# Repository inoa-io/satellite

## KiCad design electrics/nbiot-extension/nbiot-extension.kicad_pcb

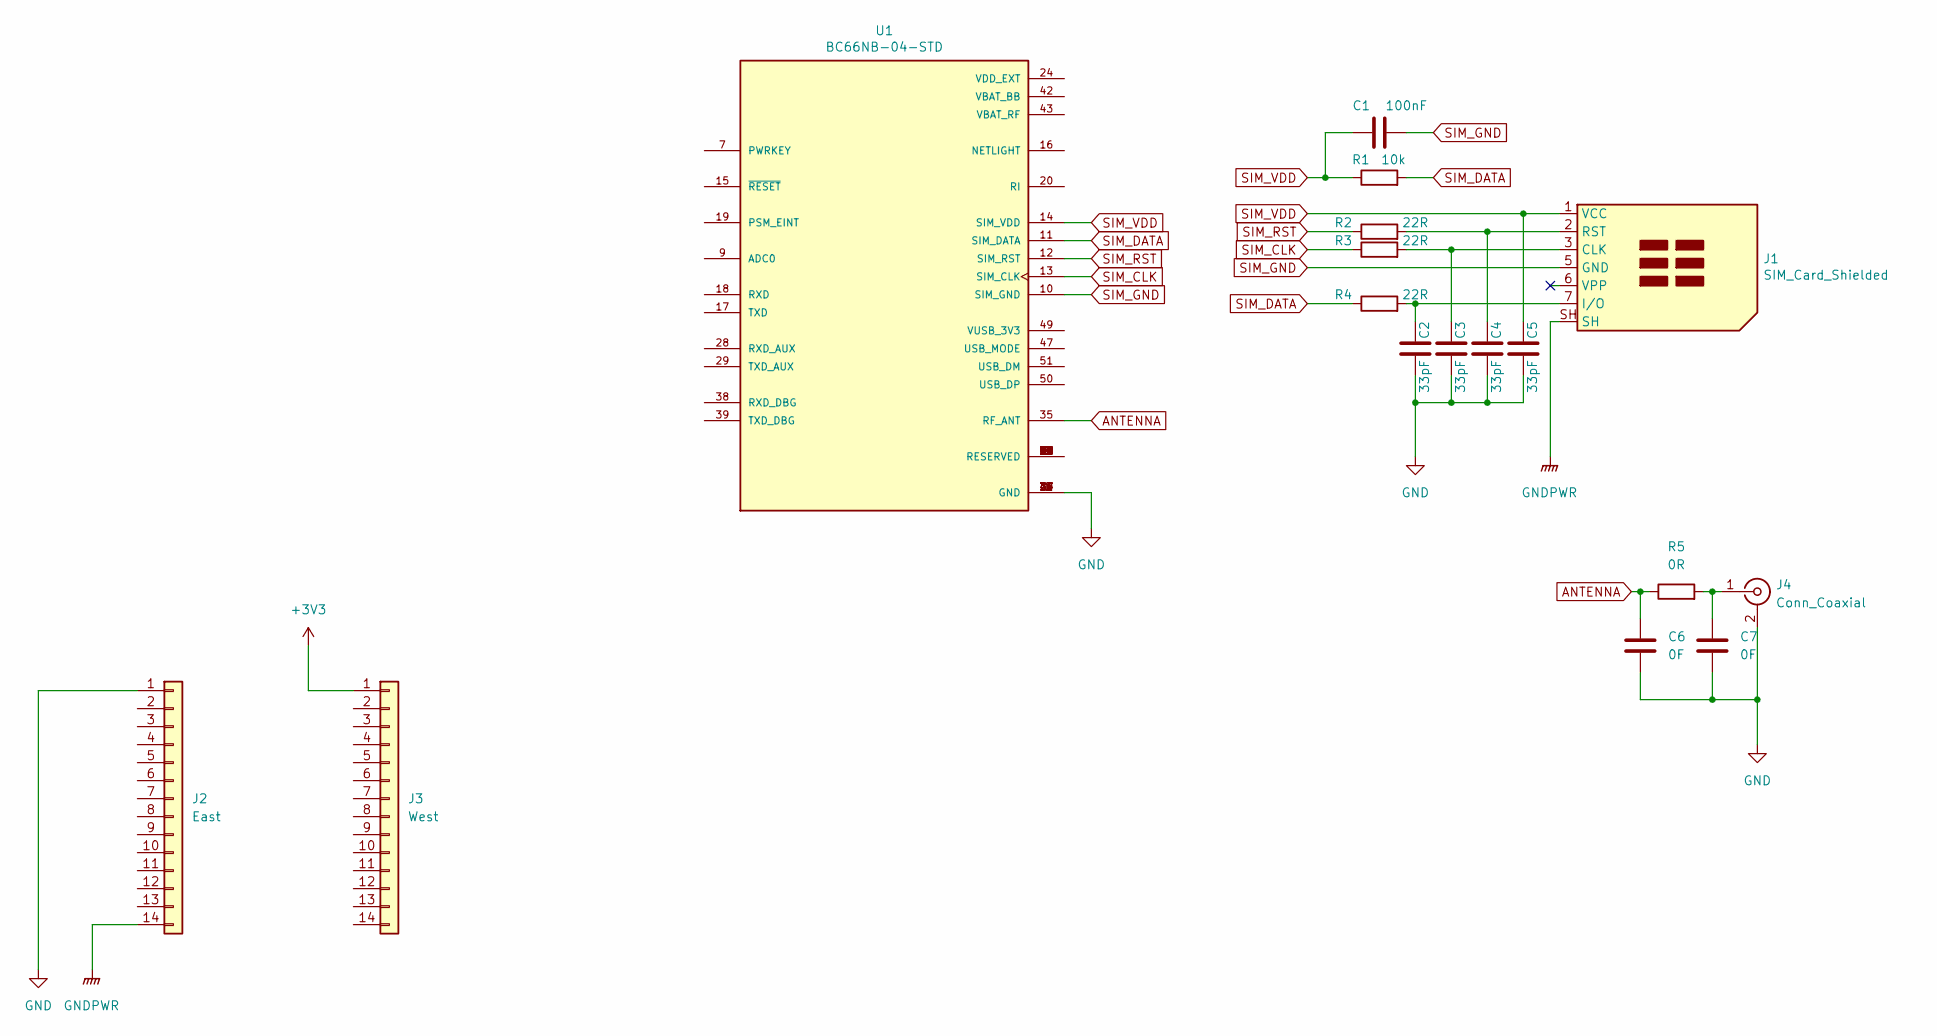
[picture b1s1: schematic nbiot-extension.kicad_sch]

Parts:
C1: 100nF; C_1206_3216Metric_Pad1.33x1.80mm_HandSolder
C2, C3, C4, C5: 33pF; C_1206_3216Metric_Pad1.33x1.80mm_HandSolder
C6, C7: 0F; C_0603_1608Metric_Pad1.08x0.95mm_HandSolder
J1: SIM_Card_Shielded; microSIM_JAE_SF53S006VCBR2000
J2: East; PinHeader_1x14_P2.54mm_Vertical
J3: West; PinHeader_1x14_P2.54mm_Vertical
J4: Conn_Coaxial; U.FL_Hirose_U.FL-R-SMT-1_Vertical
R1: 10k; R_1206_3216Metric_Pad1.30x1.75mm_HandSolder
R2, R3, R4: 22R; R_1206_3216Metric_Pad1.30x1.75mm_HandSolder
R5: 0R; R_0603_1608Metric_Pad0.98x0.95mm_HandSolder
U1: BC66NB-04-STD; XCVR_BC66NB-04-STD

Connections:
+3V3: J3.1
ANTENNA: C6.1, R5.1, U1.35 (RF_ANT); also elsewhere on the board
GND: C2.2, C3.2, C4.2, C5.2, C6.2, C7.2, J2.1, J4.2 (Ext), U1.1 (GND), U1.27 (GND), U1.34 (GND), U1.36 (GND), U1.37 (GND), U1.40 (GND), U1.41 (GND)
GNDPWR: J1.SH, J2.14
unnamed: C2.1, J1.7 (I/O), R4.2
unnamed: C3.1, J1.3 (CLK), R3.2
unnamed: C4.1, J1.2 (RST), R2.2
unnamed 7: C7.1, J4.1 (In), R5.2; also elsewhere on the board
unnamed: U1.2 (RESERVED), U1.3 (RESERVED), U1.4 (RESERVED), U1.5 (RESERVED), U1.6 (RESERVED), U1.8 (RESERVED), U1.21 (RESERVED), U1.22 (RESERVED), U1.23 (RESERVED), U1.25 (RESERVED), U1.26 (RESERVED), U1.30 (RESERVED), U1.31 (RESERVED), U1.32 (RESERVED), U1.33 (RESERVED), U1.44 (RESERVED), U1.45 (RESERVED), U1.46 (RESERVED), U1.48 (RESERVED), U1.52 (RESERVED), U1.53 (RESERVED), U1.54 (RESERVED), U1.55 (RESERVED), U1.56 (RESERVED), U1.57 (RESERVED), U1.58 (RESERVED)
SIM_CLK: R3.1, U1.13 (SIM_CLK)
SIM_DATA: R1.2, R4.1, U1.11 (SIM_DATA)
SIM_GND: C1.2, J1.5 (GND), U1.10 (SIM_GND)
SIM_RST: R2.1, U1.12 (SIM_RST)
SIM_VDD: C1.1, C5.1, J1.1 (VCC), R1.1, U1.14 (SIM_VDD)

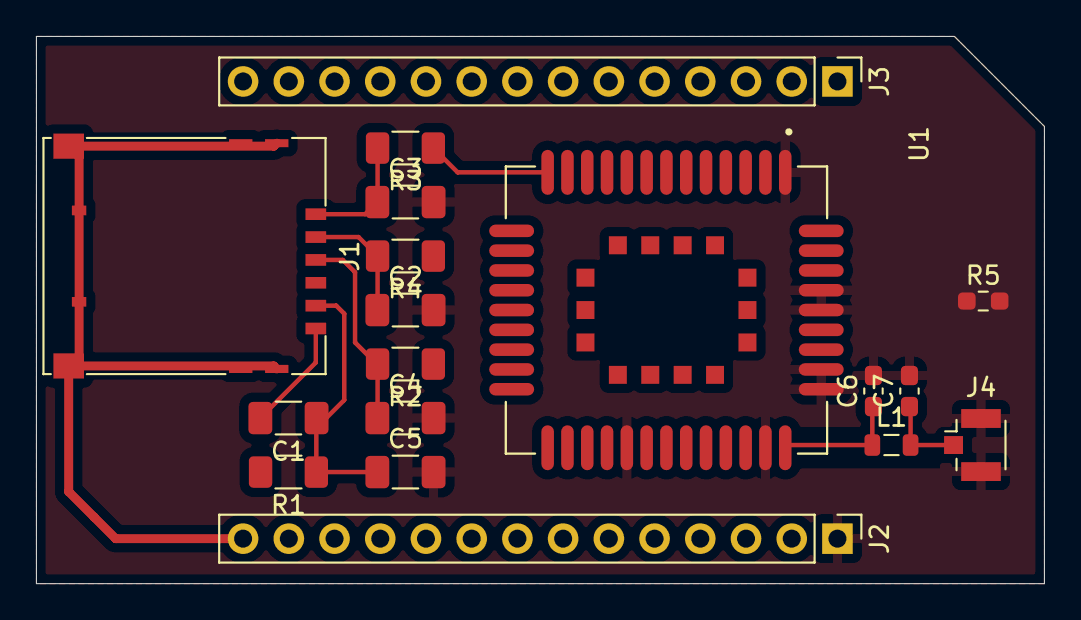
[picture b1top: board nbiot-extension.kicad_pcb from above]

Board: 2 copper layers, 56.0 x 30.4 mm, 18 parts (0 on the bottom side), 13 nets.

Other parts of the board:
L1: L; L_0805_2012Metric

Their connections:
ANTENNA: L1.1; also elsewhere on the board
unnamed 7: L1.2; also elsewhere on the board

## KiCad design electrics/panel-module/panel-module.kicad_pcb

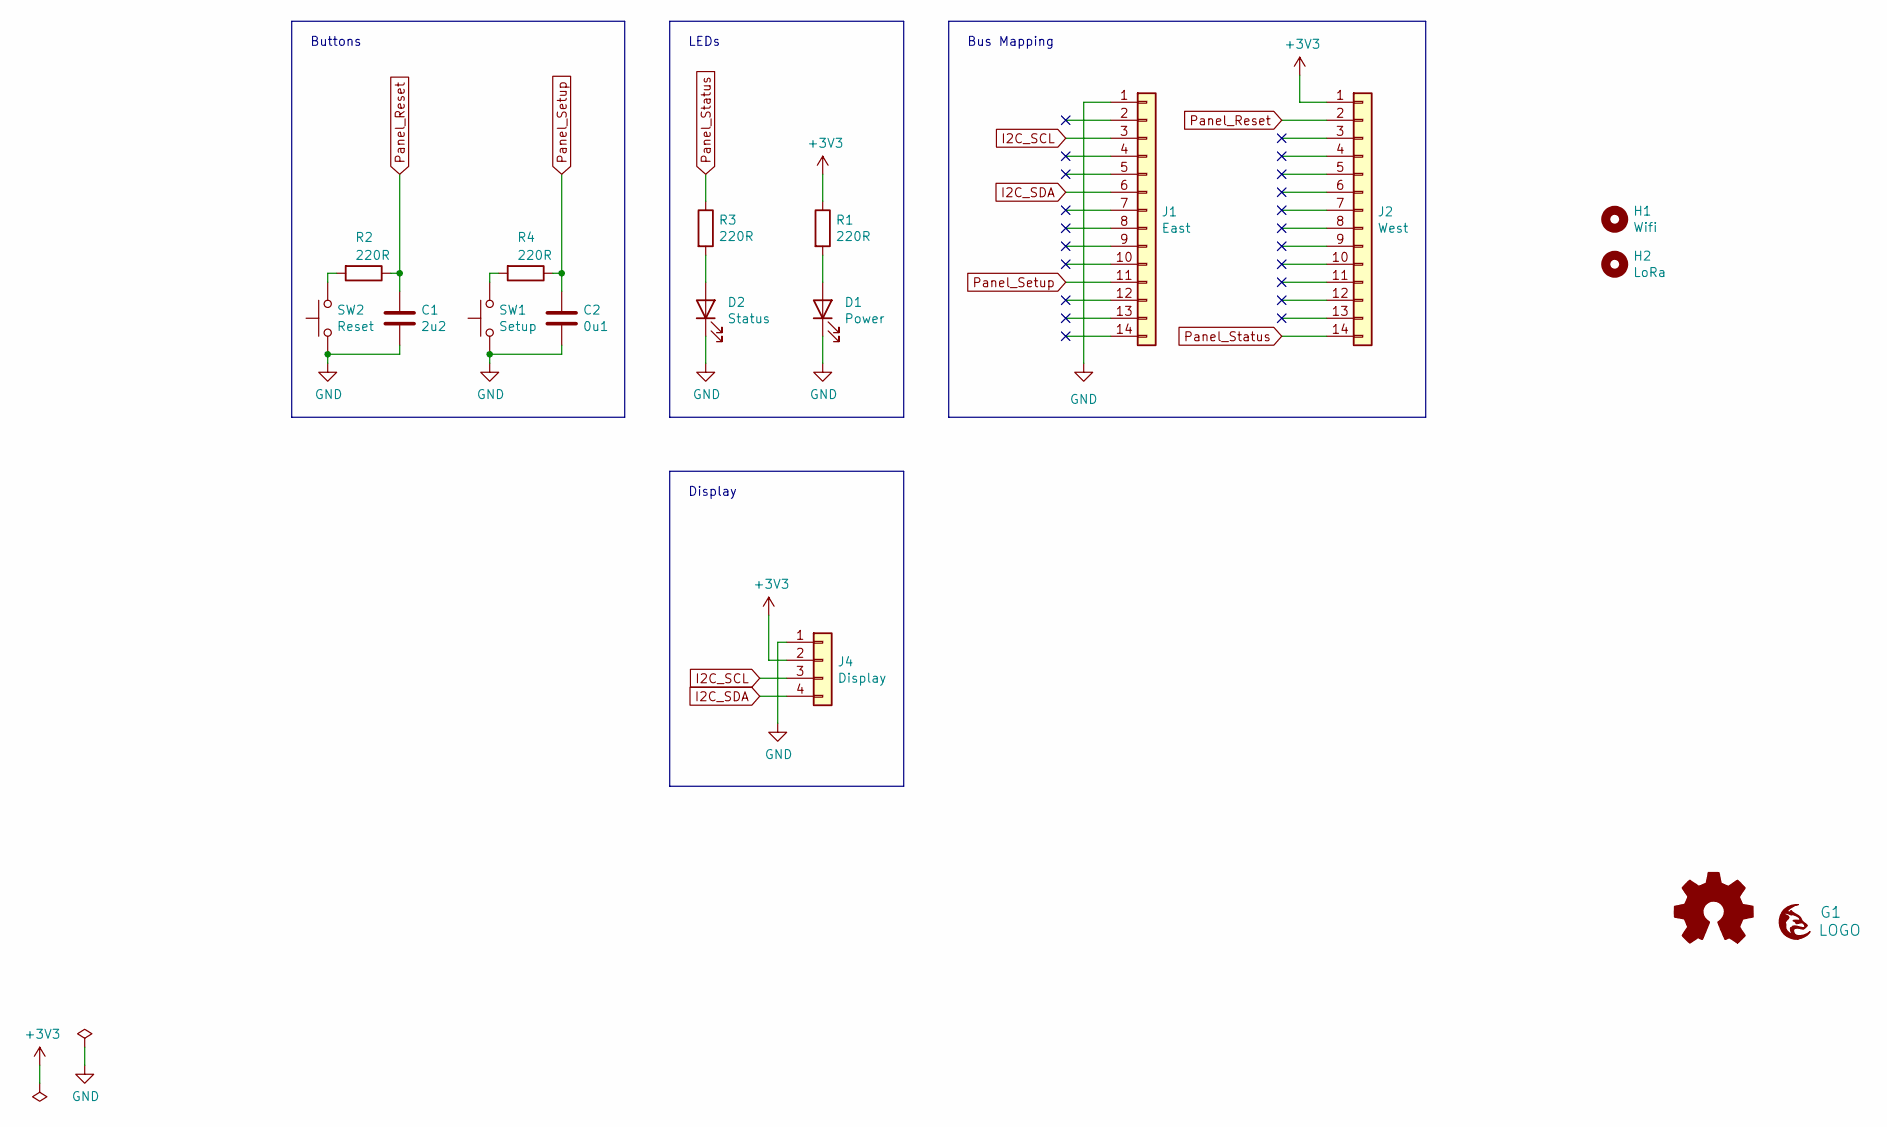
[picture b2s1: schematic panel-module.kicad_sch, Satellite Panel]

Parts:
C1: 2u2; C_1206_3216Metric_Pad1.33x1.80mm_HandSolder; mouser# 963-TMK316BJ225KD-T
C2: 0u1; C_1206_3216Metric_Pad1.33x1.80mm_HandSolder
D1: Power; LED_1206_3216Metric_Pad1.42x1.75mm_HandSolder_With_Cover; part-num SML-LXL1206GC-TR; mouser# 696-SML-L1206GCTR
D2: Status; LED_1206_3216Metric_Pad1.42x1.75mm_HandSolder_With_Cover; part-num SML-LXL1206GC-TR; mouser# 696-SML-L1206GCTR
G1: LOGO; grayc-logo-negative
G2: Logo_Open_Hardware_Small; OSHW-Logo2_7.3x6mm_SilkScreen
H1: Wifi; MountingHole_6.4mm_M6
H2: LoRa; MountingHole_6.4mm_M6
J1: East; PinSocket_1x14_P2.54mm_Vertical
J2: West; PinSocket_1x14_P2.54mm_Vertical
J4: Display; PinHeader_1x04_P2.54mm_Vertical
R1, R2, R3, R4: 220R; R_1206_3216Metric_Pad1.30x1.75mm_HandSolder; part-num RCG1206220RJNEA; mouser# 71-RCG1206220RJNEA
SW1: Setup; SW_SPST_PTS645; mouser# 611-RS014R05B1SMA10R
SW2: Reset; SW_SPST_PTS645; mouser# 611-RS014R05B1SMA10R

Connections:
+3V3: J2.1, J4.2, R1.1
GND: C1.2, C2.2, D1.1 (K), D2.1 (K), J1.1, J4.1, SW1.1, SW2.1
I2C_SCL: J1.3, J4.3
I2C_SDA: J1.6, J4.4
unnamed: D1.2 (A), R1.2
unnamed: D2.2 (A), R3.2
unnamed: R2.2, SW2.2
unnamed: R4.2, SW1.2
Panel_Reset: C1.1, J2.2, R2.1
Panel_Setup: C2.1, J1.11, R4.1
Panel_Status: J2.14, R3.1

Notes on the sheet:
Buttons
Bus Mapping
LEDs
Display

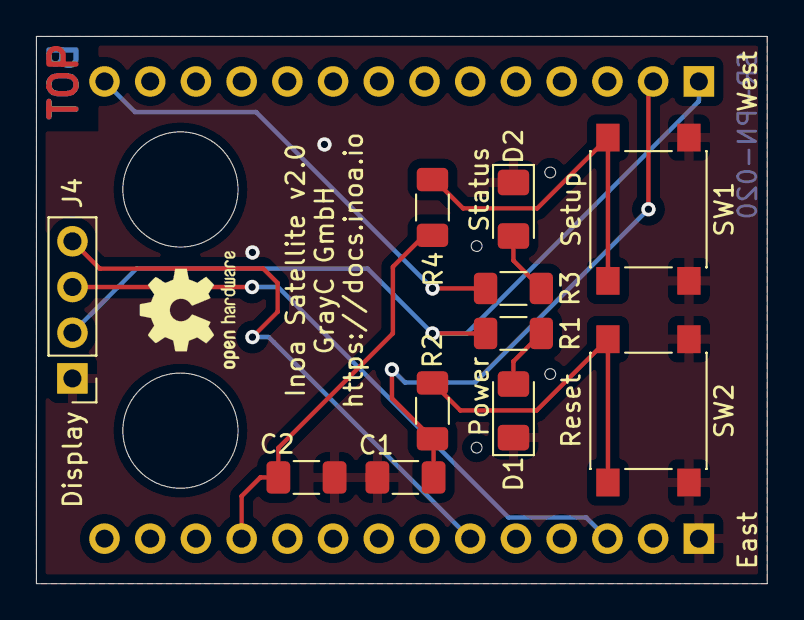
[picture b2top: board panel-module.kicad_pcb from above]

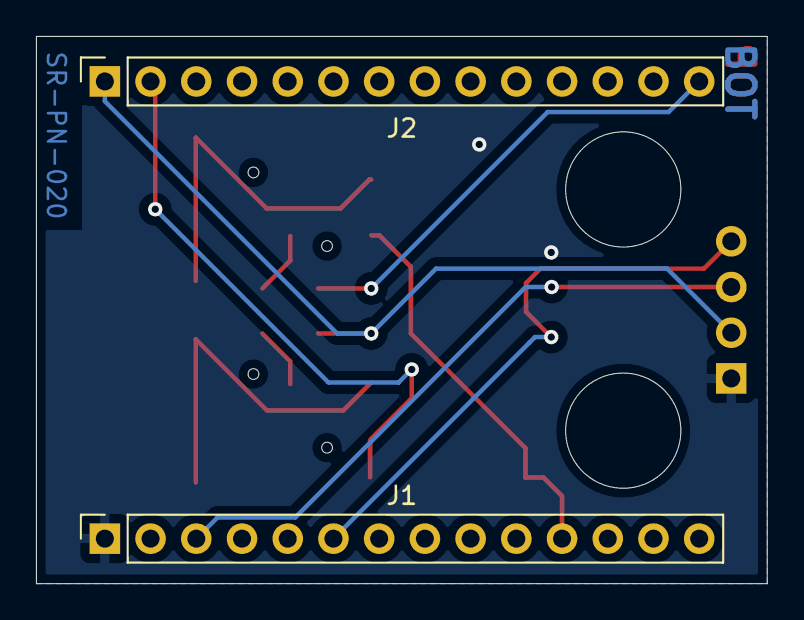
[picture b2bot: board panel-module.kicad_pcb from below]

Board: 2 copper layers, 40.6 x 30.4 mm, 17 parts (3 on the bottom side), 11 nets.

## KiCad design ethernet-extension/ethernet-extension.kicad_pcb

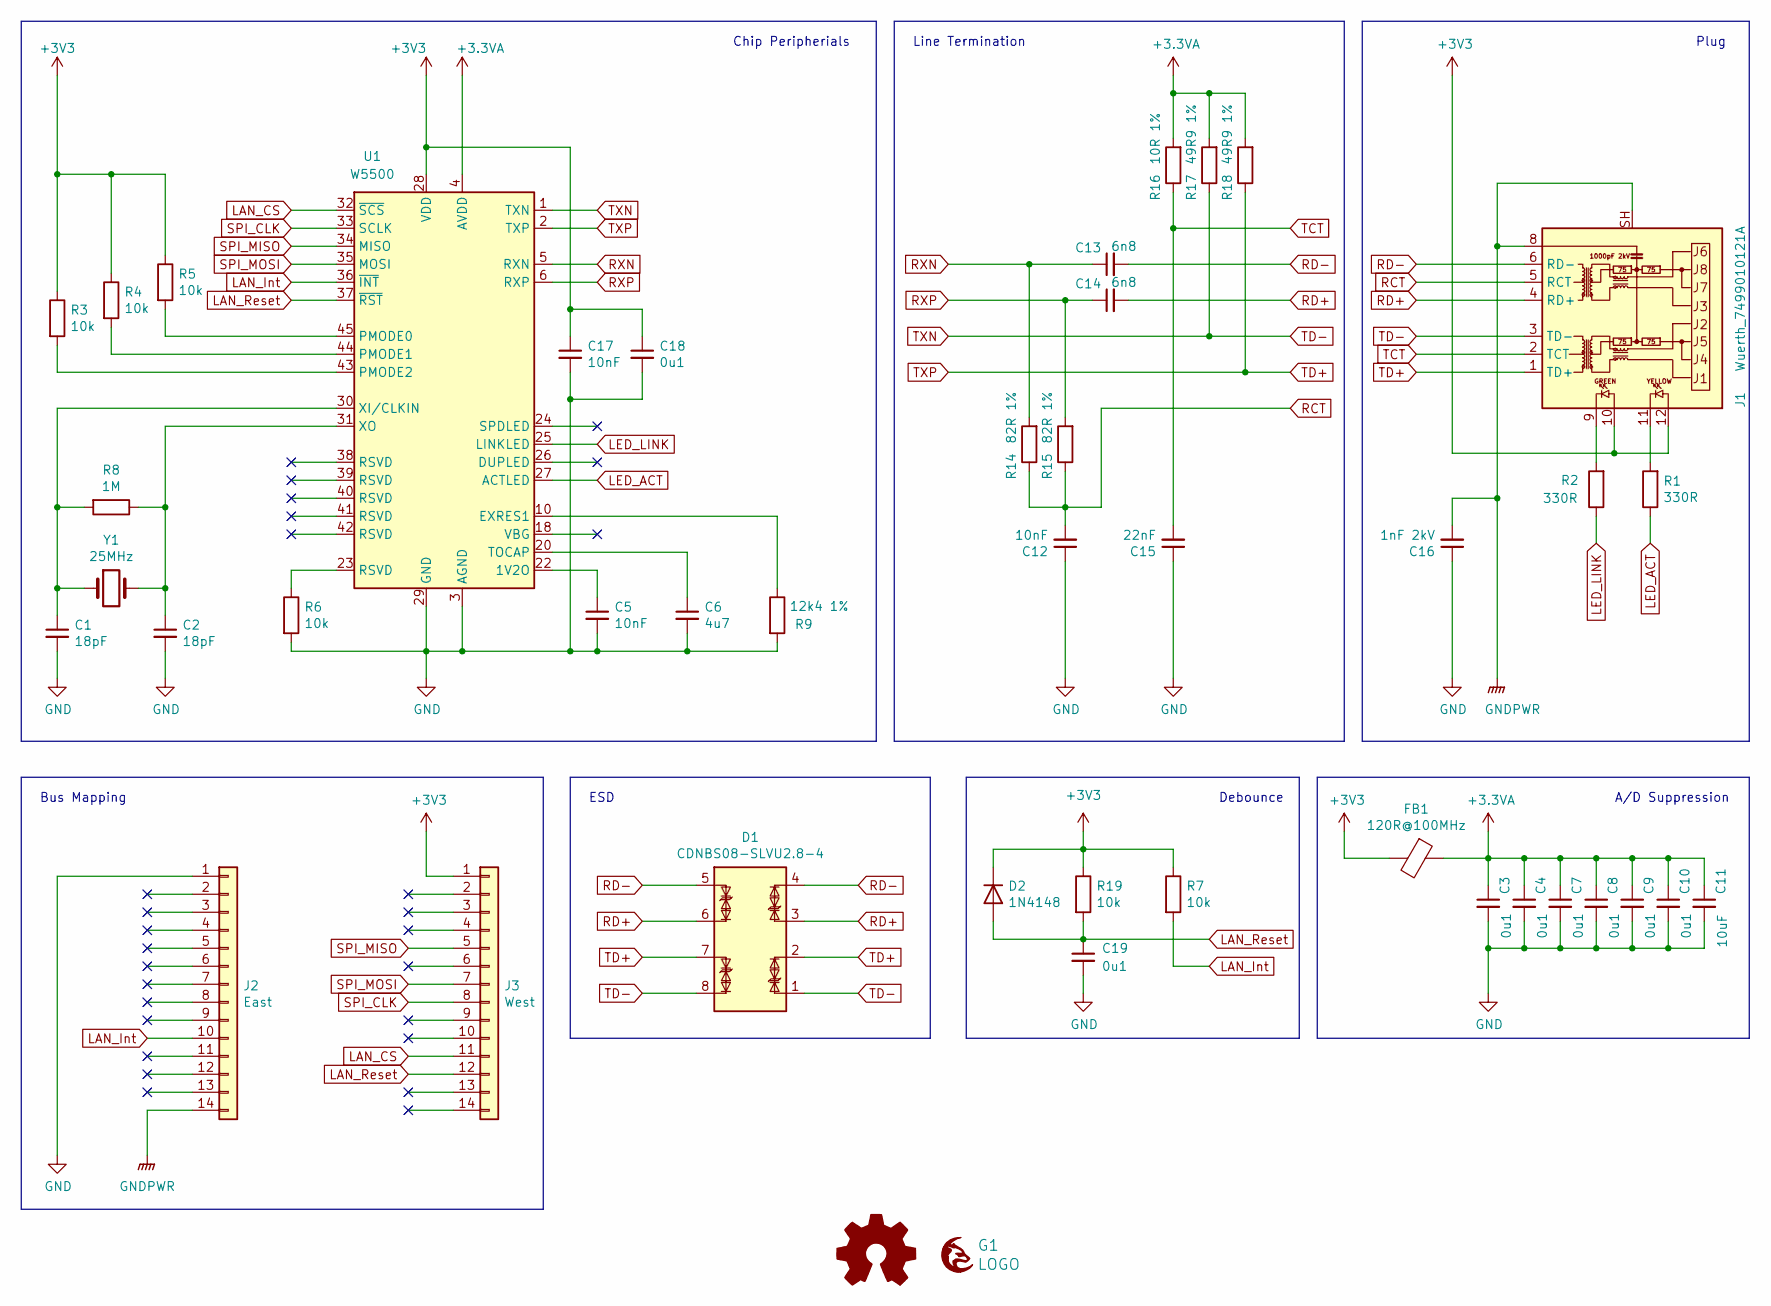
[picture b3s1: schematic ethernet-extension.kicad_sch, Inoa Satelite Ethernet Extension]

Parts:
C1, C2: 18pF; C_0603_1608Metric_Pad1.08x0.95mm_HandSolder
C3, C4, C7, C8, C9, C10, C18, C19: 0u1; C_0603_1608Metric_Pad1.08x0.95mm_HandSolder
C5, C12, C17: 10nF; C_0603_1608Metric_Pad1.08x0.95mm_HandSolder
C6: 4u7; C_0603_1608Metric_Pad1.08x0.95mm_HandSolder
C11: 10uF; C_0603_1608Metric_Pad1.08x0.95mm_HandSolder
C13, C14: 6n8; C_0603_1608Metric_Pad1.08x0.95mm_HandSolder
C15: 22nF; C_0603_1608Metric_Pad1.08x0.95mm_HandSolder
C16: 1nF 2kV; C_1812_4532Metric_Pad1.57x3.40mm_HandSolder
D1: CDNBS08-SLVU2.8-4; SOIC-8_3.9x4.9mm_P1.27mm
D2: 1N4148; D_SOD-323_HandSoldering
FB1: 120R@100MHz; L_0805_2012Metric
G1: LOGO; grayc-logo-negative
G2: Logo_Open_Hardware_Small; OSHW-Logo2_7.3x6mm_SilkScreen
J1: Wuerth_7499010121A; RJ45_Wuerth_7499010121A_Horizontal
J2: East; PinHeader_1x14_P2.54mm_Vertical
J3: West; PinHeader_1x14_P2.54mm_Vertical
R1, R2: 330R; R_0603_1608Metric_Pad0.98x0.95mm_HandSolder
R3, R4, R5, R6, R7, R19: 10k; R_0603_1608Metric_Pad0.98x0.95mm_HandSolder
R8: 1M; R_0603_1608Metric_Pad0.98x0.95mm_HandSolder
R9: 12k4 1%; R_0603_1608Metric_Pad0.98x0.95mm_HandSolder
R14, R15: 82R 1%; R_0603_1608Metric_Pad0.98x0.95mm_HandSolder
R16: 10R 1%; R_0603_1608Metric_Pad0.98x0.95mm_HandSolder
R17, R18: 49R9 1%; R_0603_1608Metric_Pad0.98x0.95mm_HandSolder
U1: W5500; LQFP-48_7x7mm_P0.5mm
Y1: 25MHz; Crystal_SMD_0603-2Pin_6.0x3.5mm_HandSoldering

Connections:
+3.3VA: C3.1, C4.1, C7.1, C8.1, C9.1, C10.1, C11.1, FB1.1, R16.2, R17.2, R18.2, U1.4 (AVDD), U1.8 (AVDD), U1.11 (AVDD), U1.15 (AVDD), U1.17 (AVDD), U1.21 (AVDD)
+3V3: C17.1, C18.1, D2.1 (K), FB1.2, J1.10, J1.12, J3.1, R3.1, R4.1, R5.1, R7.1, R19.1, U1.28 (VDD)
GND: C1.2, C2.2, C3.2, C4.2, C5.2, C6.2, C7.2, C8.2, C9.2, C10.2, C11.2, C12.1, C15.1, C16.1, C17.2, C18.2, C19.2, J2.1, R6.2, R9.2, U1.3 (AGND), U1.9 (AGND), U1.14 (AGND), U1.16 (AGND), U1.19 (AGND), U1.29 (GND), U1.48 (AGND)
GNDPWR: C16.2, J1.8, J1.SH, J2.14
LAN_CS: J3.11, U1.32 (~SCS)
LAN_Int: J2.10, R7.2, U1.36 (~INT)
LAN_Reset: C19.1, D2.2 (A), J3.12, R19.2, U1.37 (~RST)
LED_ACT: R1.1, U1.27 (ACTLED)
LED_LINK: R2.1, U1.25 (LINKLED)
unnamed: C1.1, R8.2, U1.30 (XI/CLKIN), Y1.1
unnamed: C2.1, R8.1, U1.31 (XO), Y1.2
unnamed: C5.1, U1.22 (1V2O)
unnamed: C6.1, U1.20 (TOCAP)
unnamed: J1.9, R2.2
unnamed: J1.11, R1.2
unnamed: R3.2, U1.43 (PMODE2)
unnamed: R4.2, U1.44 (PMODE1)
unnamed: R5.2, U1.45 (PMODE0)
unnamed: R6.1, U1.23 (RSVD)
unnamed: R9.1, U1.10 (EXRES1)
RCT: C12.2, J1.5 (RCT), R14.1, R15.1
RD+: C14.2, D1.3 (TVS1), D1.6 (TVS2), J1.4 (RD+)
RD-: C13.2, D1.4 (TVS2), D1.5 (TVS1), J1.6 (RD-)
RXN: C13.1, R14.2, U1.5 (RXN)
RXP: C14.1, R15.2, U1.6 (RXP)
SPI_CLK: J3.8, U1.33 (SCLK)
SPI_MISO: J3.5, U1.34 (MISO)
SPI_MOSI: J3.7, U1.35 (MOSI)
TCT: C15.2, J1.2 (TCT), R16.1
TD+: D1.2 (TVS2), D1.7 (TVS1), J1.1 (TD+), R18.1, U1.2 (TXP)
TD-: D1.1 (TVS1), D1.8 (TVS2), J1.3 (TD-), R17.1, U1.1 (TXN)

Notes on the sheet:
ESD
Debounce
A/D Suppression
Chip Peripherials
Plug
Line Termination
Bus Mapping

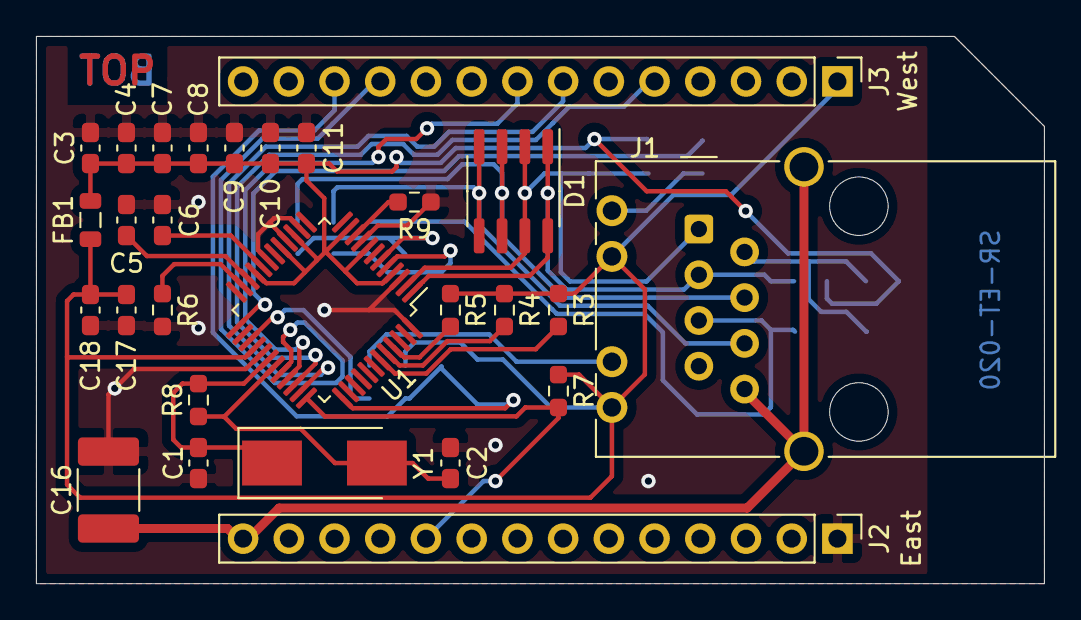
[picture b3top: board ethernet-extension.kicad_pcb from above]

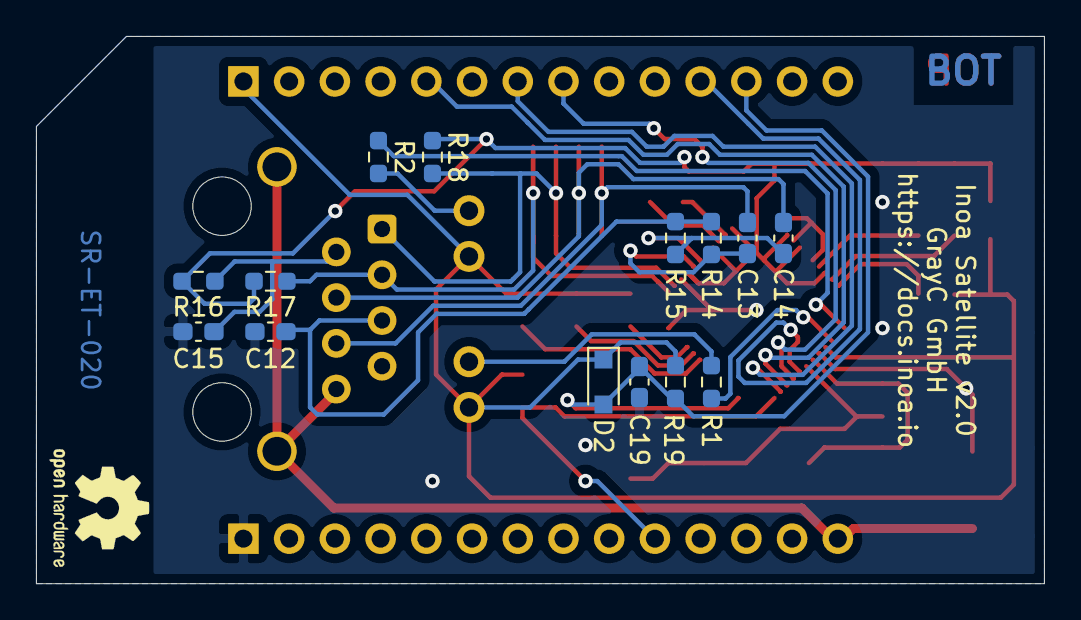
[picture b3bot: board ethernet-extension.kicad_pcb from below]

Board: 2 copper layers, 56.0 x 30.4 mm, 44 parts (16 on the bottom side), 31 nets.

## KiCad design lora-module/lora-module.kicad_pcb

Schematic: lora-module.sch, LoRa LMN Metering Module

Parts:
C1: 100nF/35V; C_1206_3216Metric_Pad1.33x1.80mm_HandSolder
C2: 0u1; C_1206_3216Metric_Pad1.33x1.80mm_HandSolder
C3, C4, C5, C7: 100nF; C_1206_3216Metric_Pad1.33x1.80mm_HandSolder
C6: 47uF; CP_Elec_5x5.3
D1: 25V; D_SOD-523
D2, D5: 1N5819; D_SOD-323_HandSoldering
D3: D_TVS; D_0603_1608Metric_Pad1.05x0.95mm_HandSolder
D4: 13V; D_SOD-523
F1: 25V/1A; Fuse_1206_3216Metric_Pad1.42x1.75mm_HandSolder
F2: 13V/2A; Fuse_1206_3216Metric_Pad1.42x1.75mm_HandSolder
G1: LOGO; grayc-logo-negative
G2: Logo_Open_Hardware_Small; OSHW-Logo2_7.3x6mm_SilkScreen
H1: Antenna; MountingHole_3.7mm
J1: RJ12; CUI_CRJ030-G-TH
J2: South; PHOENIX_1727078
J3: West; PinHeader_1x14_P2.54mm_Vertical
J4: East; PinHeader_1x14_P2.54mm_Vertical
J5: LoRa SMA; LINX_CONSMA002
J6: LoRa I-PEX; SAMTEC_RSP-122811-01; PARTREV H
R1: 220R; R_1206_3216Metric_Pad1.30x1.75mm_HandSolder
R2, R5: 10k; R_1206_3216Metric_Pad1.30x1.75mm_HandSolder
R3, R4, R6, R7, R8, R9: 0R; R_1206_3216Metric_Pad1.30x1.75mm_HandSolder
U1: MCP23009-E_SS; SOP65P780X200-20N; PARTREV C
U3: BA033CC0FP-E2; TO-252-3_TabPin2
U4, U5: MAX3486; SOIC-8_3.9x4.9mm_P1.27mm
U7: RFM95W-868S2; XCVR_RFM69HW-868S2

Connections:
+3V3: C2.1, C3.1, C4.1, C5.1, C6.1, C7.1, J3.1, U1.1, U3.3 (Output), U4.8 (VCC), U5.8 (VCC), U7.13 (3.3V)
+12V: D5.1 (K), J1.2
GND: C1.2, C2.2, C3.2, C4.2, C5.2, C6.2, C7.2, D1.2 (A), D3.2 (A2), J2.3, J4.1, R5.2, U1.20, U3.2 (GND), U4.5 (GND), U5.5 (GND), U7.1 (GND), U7.8 (GND), U7.10 (GND)
GND1: D4.2 (A), J1.3, J2.6, R2.2
GNDPWR: J2.4, J4.14, J5.2 (Ext), J6.G1, J6.G2
I2C_Int: J3.3, U1.7
I2C_SCL: J4.3, U1.3
I2C_SDA: J4.6, U1.4
LoRa_CS: J3.13, U7.5 (NSS)
LoRa_DIO0: U7.14 (DIO0)
LoRa_DIO1: U1.9, U7.15 (DIO1)
LoRa_DIO2: U1.8, U7.16 (DIO2)
LoRa_DIO3: U7.11 (DIO3)
LoRa_DIO4: U7.12 (DIO4)
LoRa_DIO5: U7.7 (DIO5)
LoRa_Reset: U7.6 (RESET)
unnamed: C1.1, D2.1 (K), U3.1 (Input)
unnamed: D1.1 (K), D2.2 (A), F1.1, R5.1
unnamed: D3.1 (A1), R1.2
unnamed: D4.1 (K), D5.2 (A), F2.1, R2.1
unnamed: J3.5, R3.1
unnamed: J3.7, R4.1
unnamed: J3.8, R6.1
unnamed: J4.2, R7.1
unnamed: J4.7, R8.1
unnamed: J4.8, R9.1
unnamed: J5.1 (In), J6.1, R1.1, U7.9 (ANT)
RS485_0_A: J1.1, U5.6 (A)
RS485_0_B: J1.6, U5.7 (B)
RS485_0_RX: J3.4, U5.1 (RO)
RS485_0_TX: J3.10, U5.4 (DI)
RS485_0_TXE: J3.9, U5.2 (~RE), U5.3 (DE)
RS485_1_A: J2.7, U4.6 (A)
RS485_1_B: J2.8, U4.7 (B)
RS485_1_RX: J3.6, U4.1 (RO)
RS485_1_TX: J4.13, U4.4 (DI)
RS485_1_TXE: J4.12, U4.2 (~RE), U4.3 (DE)
SPI_CLK: R6.2, R9.2, U7.4 (SCK)
SPI_MISO: R3.2, R8.2, U7.2 (MISO)
SPI_MOSI: R4.2, R7.2, U7.3 (MOSI)
VBUS: F2.2, J2.5
VCC: F1.2, J2.1, J2.2

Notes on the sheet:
RS485
Screw Terminal
Bus Mapping

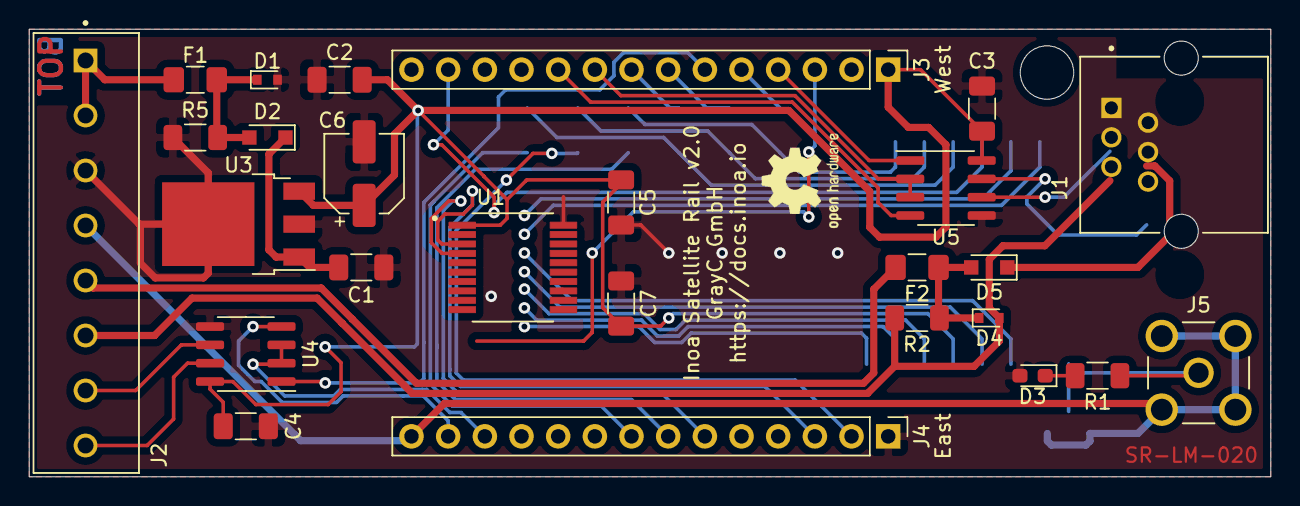
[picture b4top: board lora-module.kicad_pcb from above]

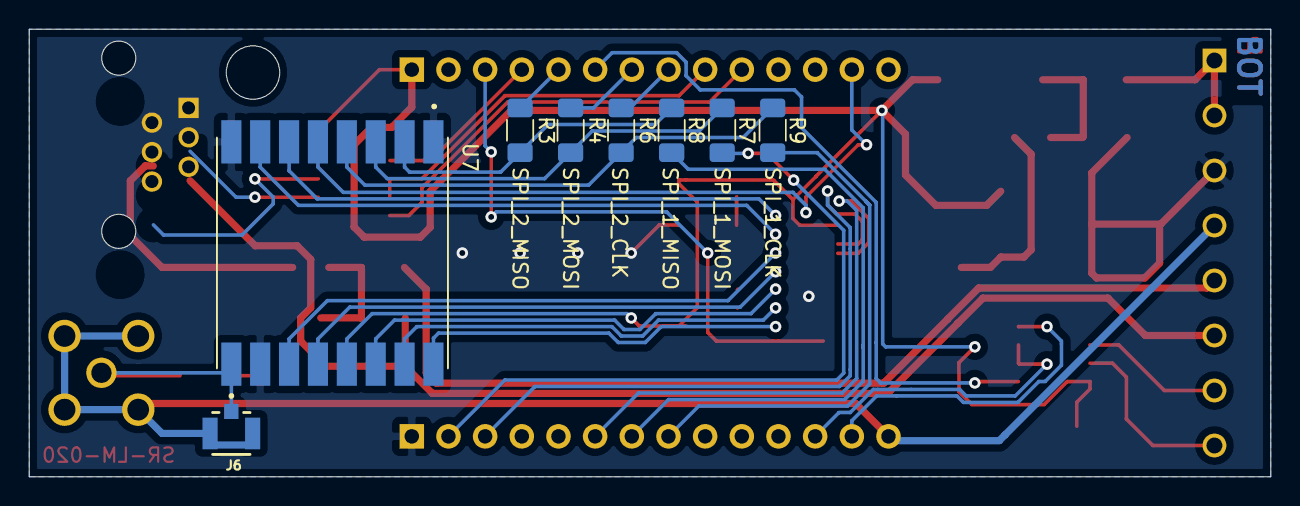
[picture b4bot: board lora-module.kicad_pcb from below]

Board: 2 copper layers, 86.0 x 31.0 mm, 37 parts (8 on the bottom side), 37 nets.

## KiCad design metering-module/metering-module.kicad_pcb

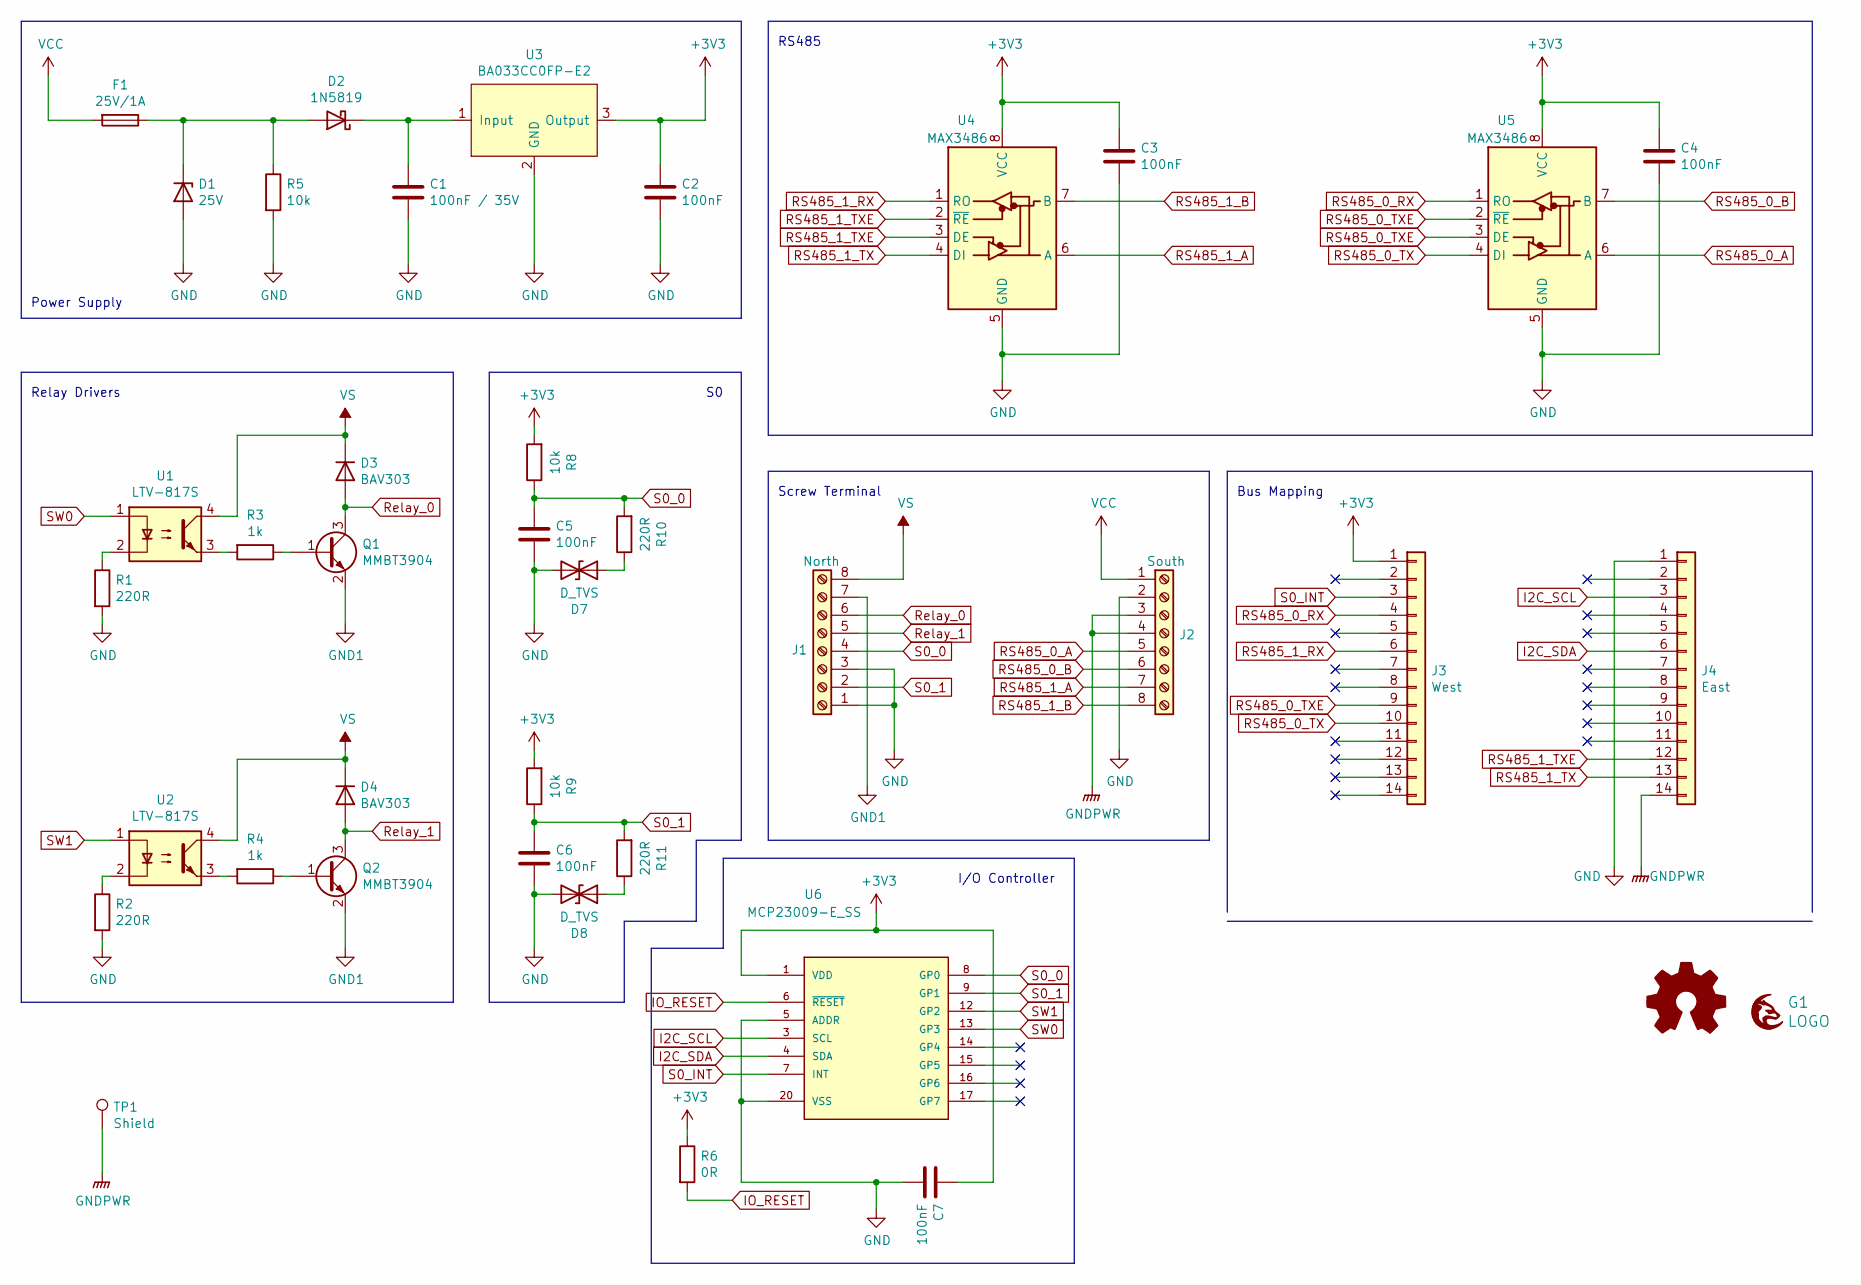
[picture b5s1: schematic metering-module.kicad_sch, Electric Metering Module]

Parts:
C1: 100nF / 35V; C_1206_3216Metric_Pad1.33x1.80mm_HandSolder
C2, C3, C4, C5, C6, C7: 100nF; C_1206_3216Metric_Pad1.33x1.80mm_HandSolder
D1: 25V; D_SOD-523
D2: 1N5819; D_DO-41_SOD81_P10.16mm_Horizontal
D3, D4: BAV303; D_MicroMELF
D7, D8: D_TVS; D_0603_1608Metric_Pad1.05x0.95mm_HandSolder
F1: 25V/1A; Fuse_1206_3216Metric_Pad1.42x1.75mm_HandSolder
G1: LOGO; grayc-logo-negative
G2: Logo_Open_Hardware_Small; OSHW-Logo2_7.3x6mm_SilkScreen
J1: North; PHOENIX_1727078
J2: South; PHOENIX_1727078
J3: West; PinHeader_1x14_P2.54mm_Vertical
J4: East; PinHeader_1x14_P2.54mm_Vertical
Q1, Q2: MMBT3904; SOT-23
R1, R2, R10, R11: 220R; R_1206_3216Metric_Pad1.30x1.75mm_HandSolder
R3, R4: 1k; R_1206_3216Metric_Pad1.30x1.75mm_HandSolder
R5, R8, R9: 10k; R_1206_3216Metric_Pad1.30x1.75mm_HandSolder
R6: 0R; R_1206_3216Metric_Pad1.30x1.75mm_HandSolder
TP1: Shield; TestPoint_Pad_D4.0mm
U1, U2: LTV-817S; SMDIP-4_W9.53mm
U3: BA033CC0FP-E2; TO-252-3_TabPin2
U4, U5: MAX3486; SOIC-8_3.9x4.9mm_P1.27mm
U6: MCP23009-E_SS; SOP65P780X200-20N

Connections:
+3V3: C2.1, C3.1, C4.1, C7.1, J3.1, R6.1, R8.2, R9.2, U3.3 (Output), U4.8 (VCC), U5.8 (VCC), U6.1 (VDD)
GND: C1.2, C2.2, C3.2, C4.2, C5.2, C6.2, C7.2, D1.2 (A), D7.2 (A2), D8.2 (A2), J1.1, J1.3, J2.2, J4.1, R1.2, R2.2, R5.2, U3.2 (GND), U4.5 (GND), U5.5 (GND), U6.5 (ADDR), U6.20 (VSS)
GND1: J1.7, Q1.2 (E), Q2.2 (E)
GNDPWR: J2.3, J2.4, J4.14, TP1.1
I2C_SCL: J4.3, U6.3 (SCL)
I2C_SDA: J4.6, U6.4 (SDA)
IO_RESET: R6.2, U6.6 (~RESET)
unnamed: C1.1, D2.1 (K), U3.1 (Input)
unnamed: D1.1 (K), D2.2 (A), F1.1, R5.1
unnamed: D7.1 (A1), R10.1
unnamed: D8.1 (A1), R11.1
unnamed: Q1.1 (B), R3.1
unnamed: Q2.1 (B), R4.1
unnamed: R1.1, U1.2
unnamed: R2.1, U2.2
unnamed: R3.2, U1.3
unnamed: R4.2, U2.3
RS485_0_A: J2.5, U5.6 (A)
RS485_0_B: J2.6, U5.7 (B)
RS485_0_RX: J3.4, U5.1 (RO)
RS485_0_TX: J3.10, U5.4 (DI)
RS485_0_TXE: J3.9, U5.2 (~RE), U5.3 (DE)
RS485_1_A: J2.7, U4.6 (A)
RS485_1_B: J2.8, U4.7 (B)
RS485_1_RX: J3.6, U4.1 (RO)
RS485_1_TX: J4.13, U4.4 (DI)
RS485_1_TXE: J4.12, U4.2 (~RE), U4.3 (DE)
Relay_0: D3.2 (A), J1.6, Q1.3 (C)
Relay_1: D4.2 (A), J1.5, Q2.3 (C)
S0_0: C5.1, J1.4, R8.1, R10.2, U6.8 (GP0)
S0_1: C6.1, J1.2, R9.1, R11.2, U6.9 (GP1)
S0_INT: J3.3, U6.7 (INT)
SW0: U1.1, U6.13 (GP3)
SW1: U2.1, U6.12 (GP2)
VCC: F1.2, J2.1
VS: D3.1 (K), D4.1 (K), J1.8, U1.4, U2.4

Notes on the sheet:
Relay Drivers
RS485
Screw Terminal
I/O Controller
Bus Mapping
Power Supply

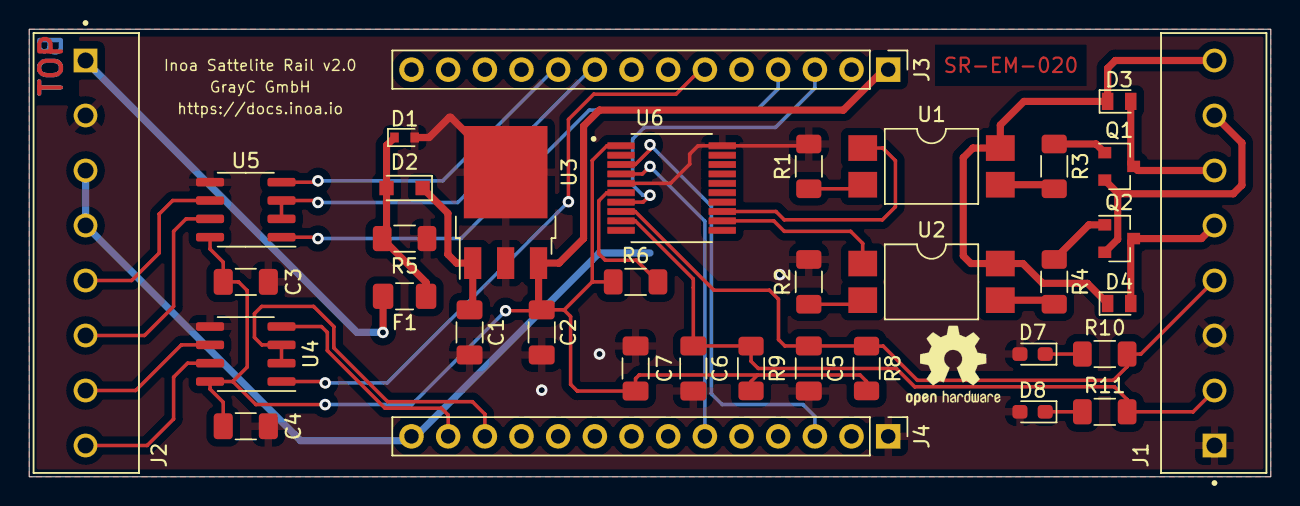
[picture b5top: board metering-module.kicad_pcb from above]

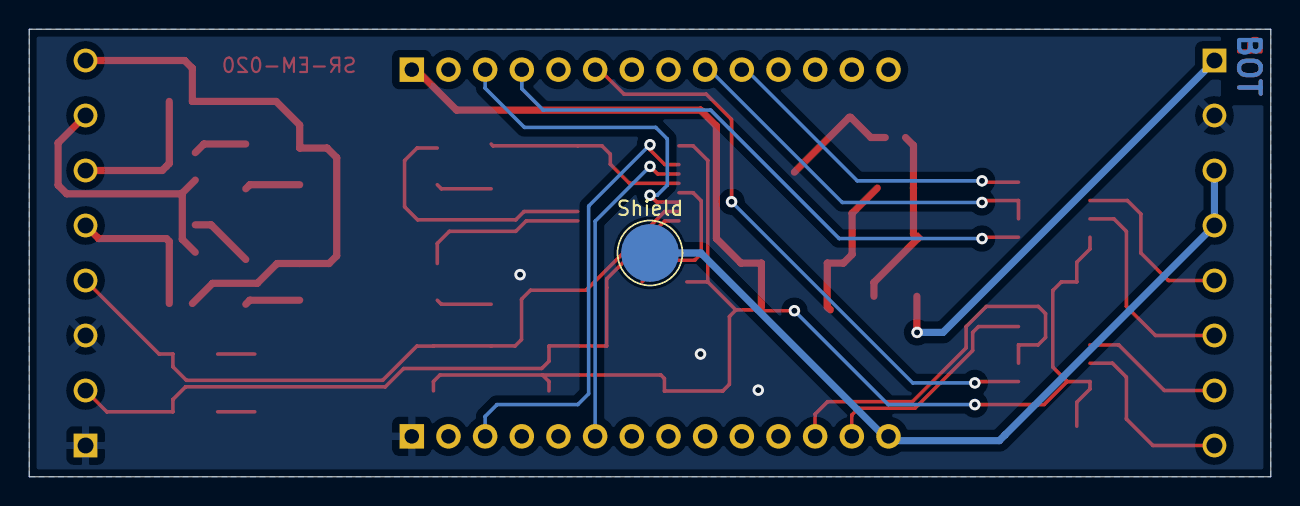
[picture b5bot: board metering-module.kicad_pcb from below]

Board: 2 copper layers, 86.0 x 31.0 mm, 39 parts (2 on the bottom side), 36 nets.

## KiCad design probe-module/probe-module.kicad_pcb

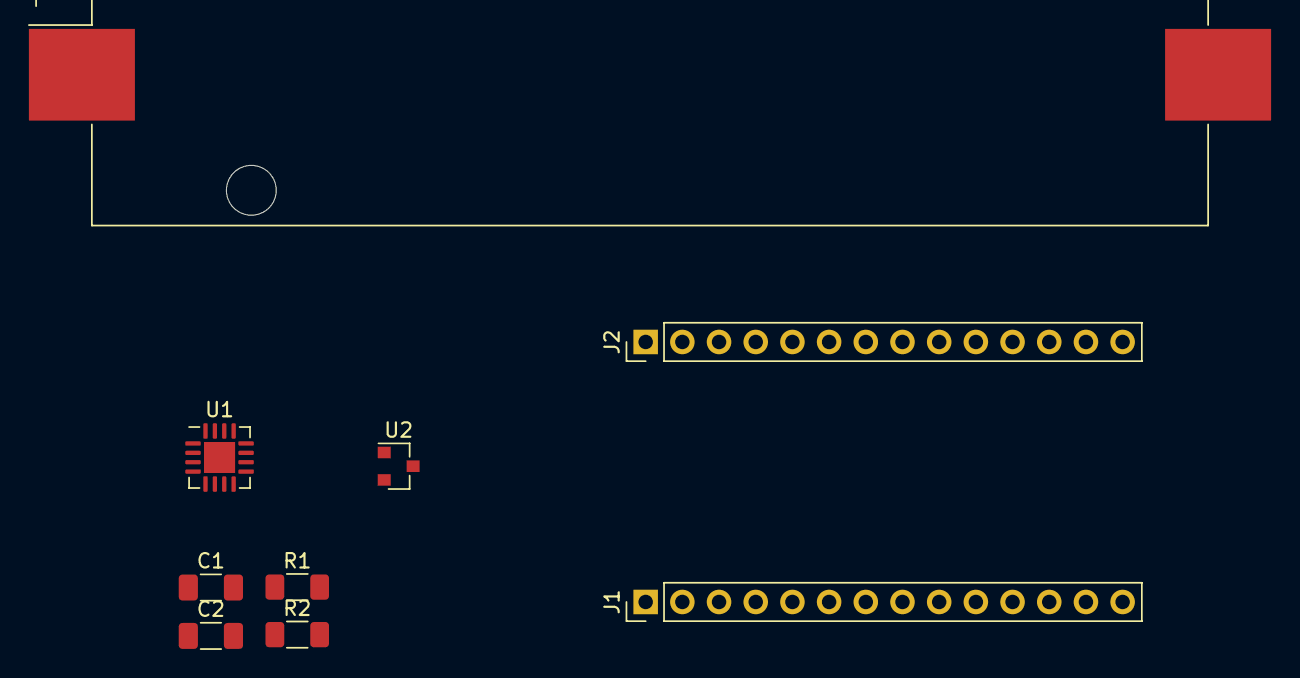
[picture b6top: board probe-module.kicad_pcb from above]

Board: 2 copper layers, 9 parts (0 on the bottom side), 2 nets, no tracks yet.

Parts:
BT1: 18650; BatteryHolder_Keystone_1042_1x18650
C1: 100nF; C_1206_3216Metric_Pad1.33x1.80mm_HandSolder
C2: 100uF; C_1206_3216Metric_Pad1.33x1.80mm_HandSolder
J1, J2: Conn_01x14; PinHeader_1x14_P2.54mm_Vertical
R1: 27k; R_1206_3216Metric_Pad1.30x1.75mm_HandSolder
R2: 100k; R_1206_3216Metric_Pad1.30x1.75mm_HandSolder
U1: LTC4055; QFN-16-1EP_4x4mm_P0.65mm_EP2.15x2.15mm
U2: MCP1700-3302E_SOT23; SOT-23

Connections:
unnamed: U1.1, U1.4
unnamed: U1.10, U1.17
